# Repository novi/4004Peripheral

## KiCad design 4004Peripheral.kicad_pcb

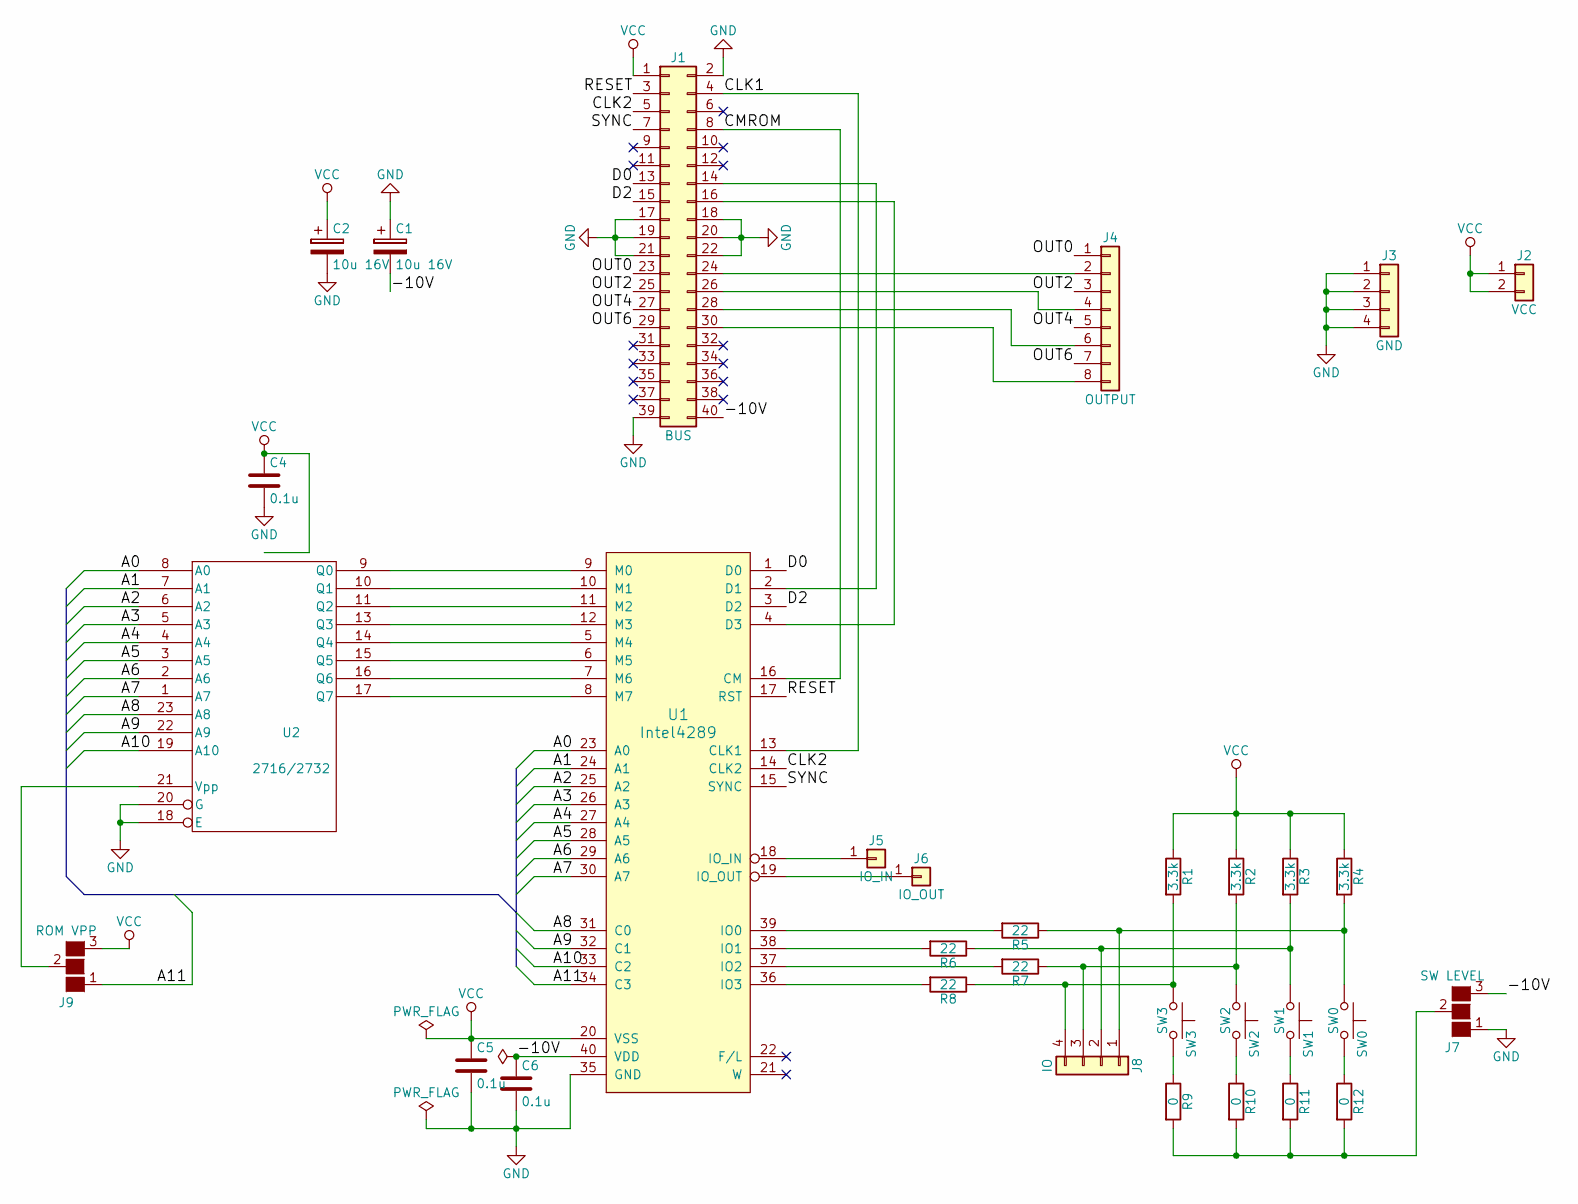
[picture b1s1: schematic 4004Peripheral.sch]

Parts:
C1, C2: 10u 16V; CP_Elec_4x4.5
C4, C5, C6: 0.1u; C_0603_HandSoldering
J1: BUS; Pin_Header_Straight_2x20_Pitch2.54mm
J2: VCC; Pin_Header_Straight_1x02_Pitch2.54mm
J3: GND; Pin_Header_Straight_1x04_Pitch2.54mm
J4: OUTPUT; Pin_Header_Straight_1x08_Pitch2.54mm
J5: IO_IN; Pin_Header_Straight_1x01_Pitch2.54mm
J6: IO_OUT; Pin_Header_Straight_1x01_Pitch2.54mm
J7: SW LEVEL; SolderJumper-3_P1.3mm_Open_RoundedPad1.0x1.5mm_NumberLabels
J8: IO; Pin_Header_Straight_1x04_Pitch2.54mm
J9: ROM VPP; SolderJumper-3_P1.3mm_Open_RoundedPad1.0x1.5mm_NumberLabels
R1, R2, R3, R4: 3.3k; R_0603_HandSoldering
R5, R6, R7, R8: 22; R_0603_HandSoldering
R9, R10, R11, R12: 0; R_0603_HandSoldering
SW0: SW0; SW_PUSH_6mm
SW1: SW1; SW_PUSH_6mm
SW2: SW2; SW_PUSH_6mm
SW3: SW3; SW_PUSH_6mm
U1: Intel4289; DIP-40_W15.24mm_Socket
U2: 2716/2732; DIP-24_W15.24mm_Socket

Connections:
/-10V: C1.2, C6.1, J1.40, J7.3 (G3), U1.40 (VDD)
/A0: U1.23 (A0), U2.8 (A0)
/A1: U1.24 (A1), U2.7 (A1)
/A2: U1.25 (A2), U2.6 (A2)
/A3: U1.26 (A3), U2.5 (A3)
/A4: U1.27 (A4), U2.4 (A4)
/A5: U1.28 (A5), U2.3 (A5)
/A6: U1.29 (A6), U2.2 (A6)
/A7: U1.30 (A7), U2.1 (A7)
/A8: U1.31 (C0), U2.23 (A8)
/A9: U1.32 (C1), U2.22 (A9)
/A10: U1.33 (C2), U2.19 (A10)
/A11: J9.1 (G1), U1.34 (C3)
/CLK1: J1.4, U1.13 (CLK1)
/CLK2: J1.5, U1.14 (CLK2)
/CMROM: J1.8, U1.16 (CM)
/D0: J1.13, U1.1 (D0)
/D2: J1.15, U1.3 (D2)
/OUT0: J1.23, J4.1
/OUT2: J1.25, J4.3
/OUT4: J1.27, J4.5
/OUT6: J1.29, J4.7
/RESET: J1.3, U1.17 (RST)
/SYNC: J1.7, U1.15 (SYNC)
GND: C1.1, C2.2, C4.2, C5.2, C6.2, J1.2, J1.17, J1.18, J1.19, J1.20, J1.21, J1.22, J1.39, J3.1, J3.2, J3.3, J3.4, J7.1 (G1), U1.35 (GND), U2.12 (GND), U2.18 (E), U2.20 (G)
unnamed: J1.14, U1.2 (D1)
unnamed: J1.16, U1.4 (D3)
unnamed: J1.24, J4.2
unnamed: J1.26, J4.4
unnamed: J1.28, J4.6
unnamed: J1.30, J4.8
unnamed: J5.1, U1.18 (IO_IN)
unnamed: J6.1, U1.19 (IO_OUT)
unnamed: J7.2 (G2), R9.2, R10.2, R11.2, R12.2
unnamed: J8.1, R4.2, R5.1, SW0.1
unnamed: J8.2, R3.2, R6.1, SW1.1
unnamed: J8.3, R2.2, R7.1, SW2.1
unnamed: J8.4, R1.2, R8.1, SW3.1
unnamed: J9.2 (G2), U2.21 (Vpp)
unnamed: R5.2, U1.39 (IO0)
unnamed: R6.2, U1.38 (IO1)
unnamed: R7.2, U1.37 (IO2)
unnamed: R8.2, U1.36 (IO3)
unnamed: R9.1, SW3.2
unnamed: R10.1, SW2.2
unnamed: R11.1, SW1.2
unnamed: R12.1, SW0.2
unnamed: U1.5 (M4), U2.14 (Q4)
unnamed: U1.6 (M5), U2.15 (Q5)
unnamed: U1.7 (M6), U2.16 (Q6)
unnamed: U1.8 (M7), U2.17 (Q7)
unnamed: U1.9 (M0), U2.9 (Q0)
unnamed: U1.10 (M1), U2.10 (Q1)
unnamed: U1.11 (M2), U2.11 (Q2)
unnamed: U1.12 (M3), U2.13 (Q3)
VCC: C2.1, C4.1, C5.1, J1.1, J2.1, J2.2, J9.3 (G3), R1.1, R2.1, R3.1, R4.1, U1.20 (VSS), U2.24 (Vcc)

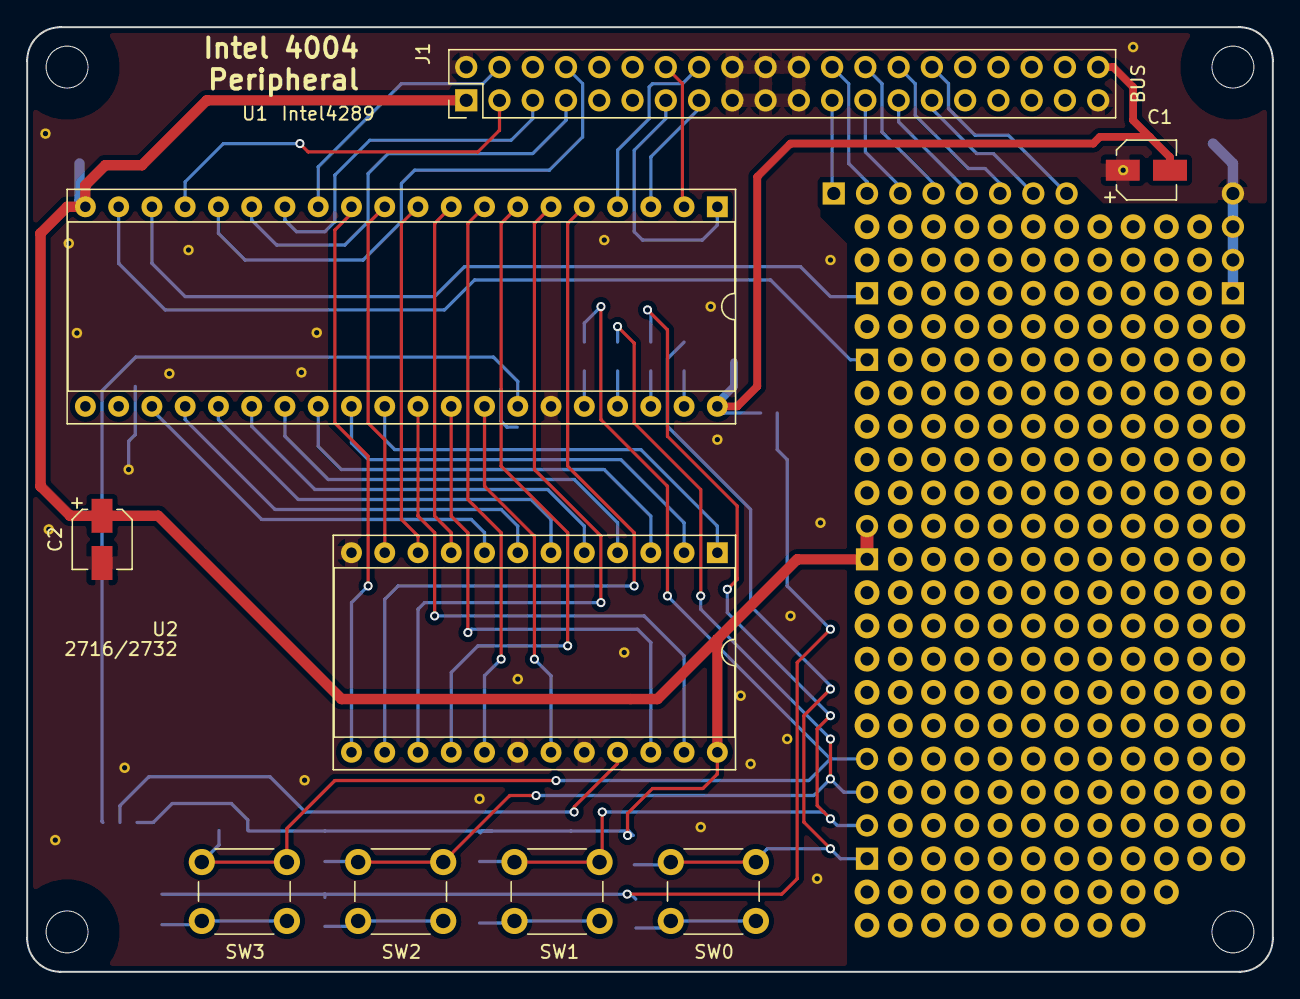
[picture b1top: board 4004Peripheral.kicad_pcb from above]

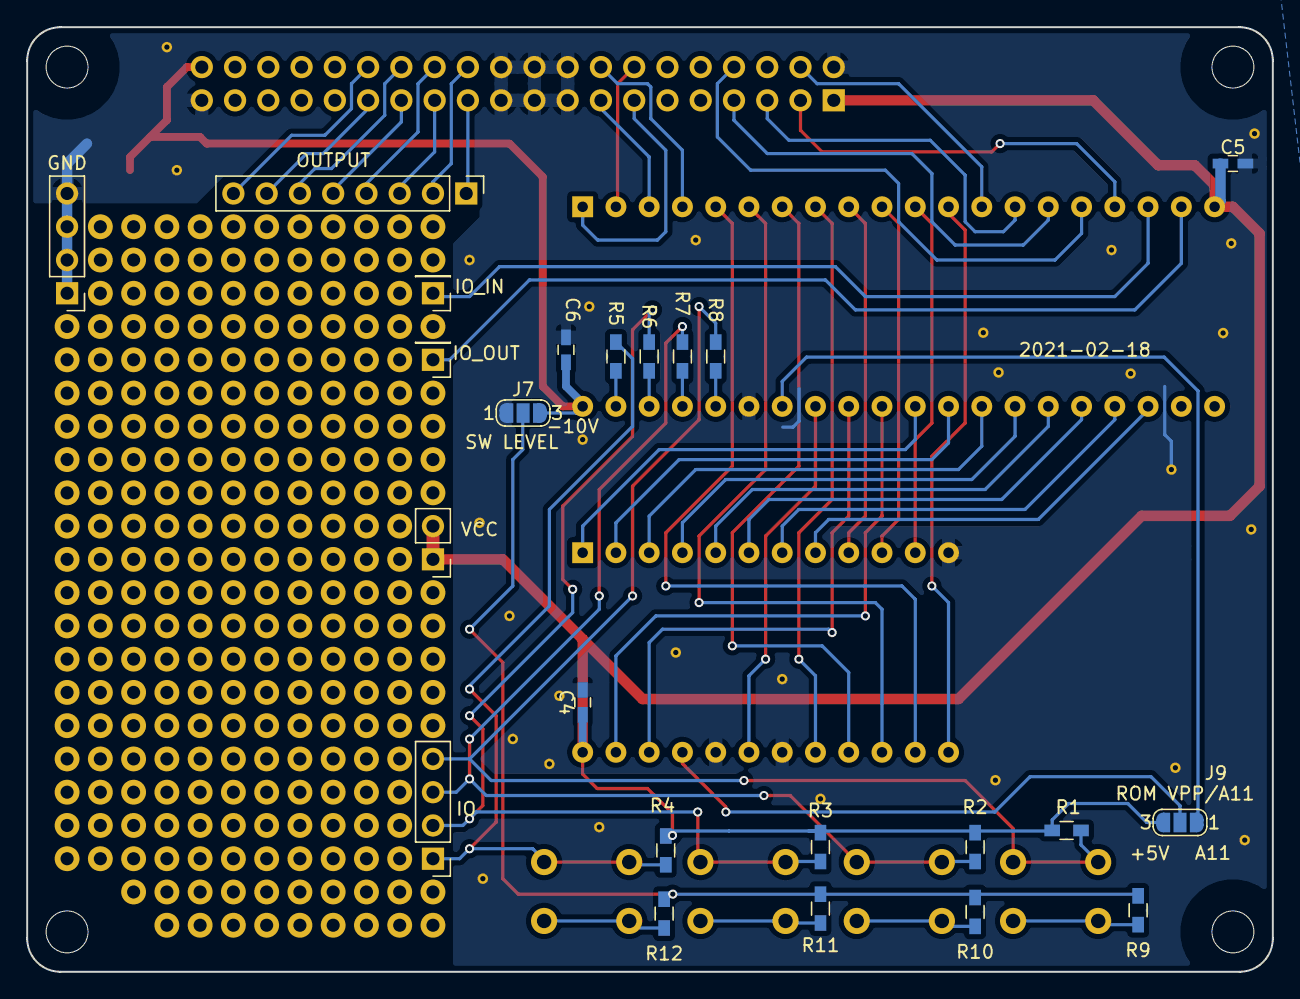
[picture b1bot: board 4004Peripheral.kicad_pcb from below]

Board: 2 copper layers, 95.1 x 72.1 mm, 32 parts (23 on the bottom side), 56 nets.

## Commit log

2018-05-13 回路を仮実装
2018-11-01 SW位置入れ替え
2021-02-01 抵抗値変更
2021-02-22 ROMサイズ選択追加
2021-02-26 minor silk change
2022-10-07 add LICENSE
